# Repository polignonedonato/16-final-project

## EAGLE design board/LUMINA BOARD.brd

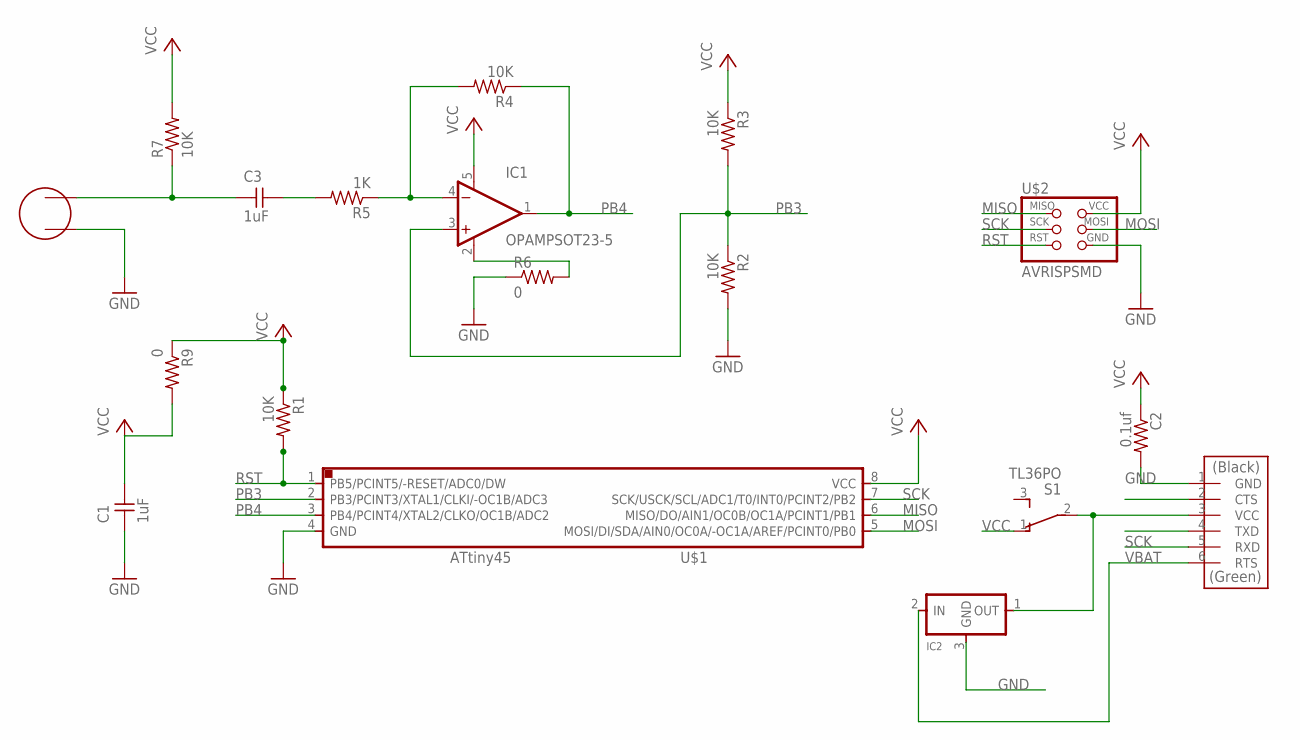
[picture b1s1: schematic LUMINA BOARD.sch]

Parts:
C1, C3: 1uF; 1206
C2: 0.1uf; 1206
IC1: OPAMPSOT23-5; SOT23-5
IC2: REGULATORSOT23; SOT23
R1, R2, R3, R4, R7: 10K; 1206
R5: 1K; 1206
R6, R9: 0; 1206
S1: TL36PO; TL3XPO
U$1: ATTINY45SI; SOIC8
U$2: AVRISPSMD; 2X03SMD
U$3: FTDI-SMD-HEADER; 1X06SMD
U$4: ELECTRET; ELECTRET_2742PBJ-A

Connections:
GND: C1.1, C2.2, IC2.3 (GND), R2.2, R6.1, U$1.4 (GND), U$2.6 (GND), U$3.1 (GND), U$4.P$1
MISO: U$1.6 (MISO/DO/AIN1/OC0B/OC1A/PCINT1/PB1), U$2.1 (MISO)
MOSI: U$1.5 (MOSI/DI/SDA/AIN0/OC0A/-OC1A/AREF/PCINT0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), U$2.4 (MOSI)
unnamed: C3.1, R7.1, U$4.P$2
unnamed: C3.2, R5.2
unnamed: IC1.4 (-IN), R4.2, R5.1
unnamed: IC1.2 (V-), R6.2
unnamed: IC2.1 (OUT), S1.2, U$3.3 (VCC)
PB3: IC1.3 (+IN), R2.1, R3.2, U$1.2 (PB3/PCINT3/XTAL1/CLKI/-OC1B/ADC3)
PB4: IC1.1 (OUT), R4.1, U$1.3 (PB4/PCINT4/XTAL2/CLKO/OC1B/ADC2)
RST: R1.2, U$1.1 (PB5/PCINT5/-RESET/ADC0/DW), U$2.5 (RST)
SCK: U$1.7 (SCK/USCK/SCL/ADC1/T0/INT0/PCINT2/PB2), U$2.3 (SCK), U$3.5 (RXD)
VBAT: IC2.2 (IN), U$3.6 (RTS)
VCC: C1.2, C2.1, IC1.5 (V+), R1.1, R3.1, R7.2, R9.1, R9.2, S1.1 (O), U$1.8 (VCC), U$2.2 (VCC)

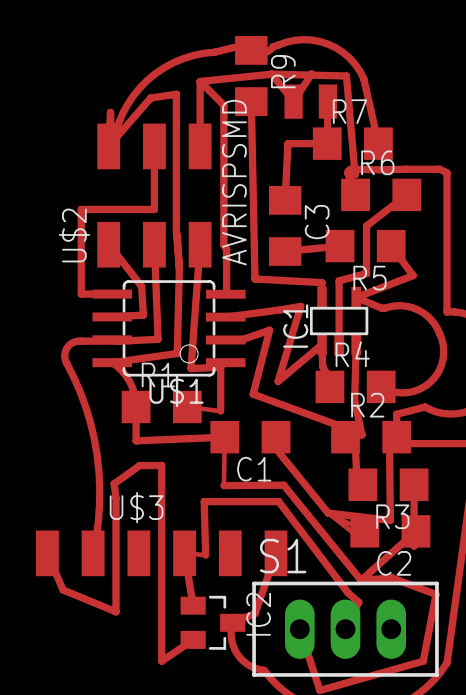
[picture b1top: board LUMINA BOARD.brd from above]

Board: 2 copper layers, 18 parts (0 on the bottom side), 14 nets.

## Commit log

2016-07-12 final project
    final project
2016-11-08 3D model necklace lumina project
    Design file 1
2016-11-08 New Necklace Beads
2016-11-08 New pendant+ sterling silver magnetic clasp
2016-11-08 3d printed test first test
2016-11-08 test
2016-11-09 Necklace.stl
2016-11-09 Add files via upload
    new design
2016-11-09 new design
2017-07-03 lumina smart gadjet board+schematic
2017-07-03 Delete final board
    delete
2017-07-03 Delete final board
    delete final board
